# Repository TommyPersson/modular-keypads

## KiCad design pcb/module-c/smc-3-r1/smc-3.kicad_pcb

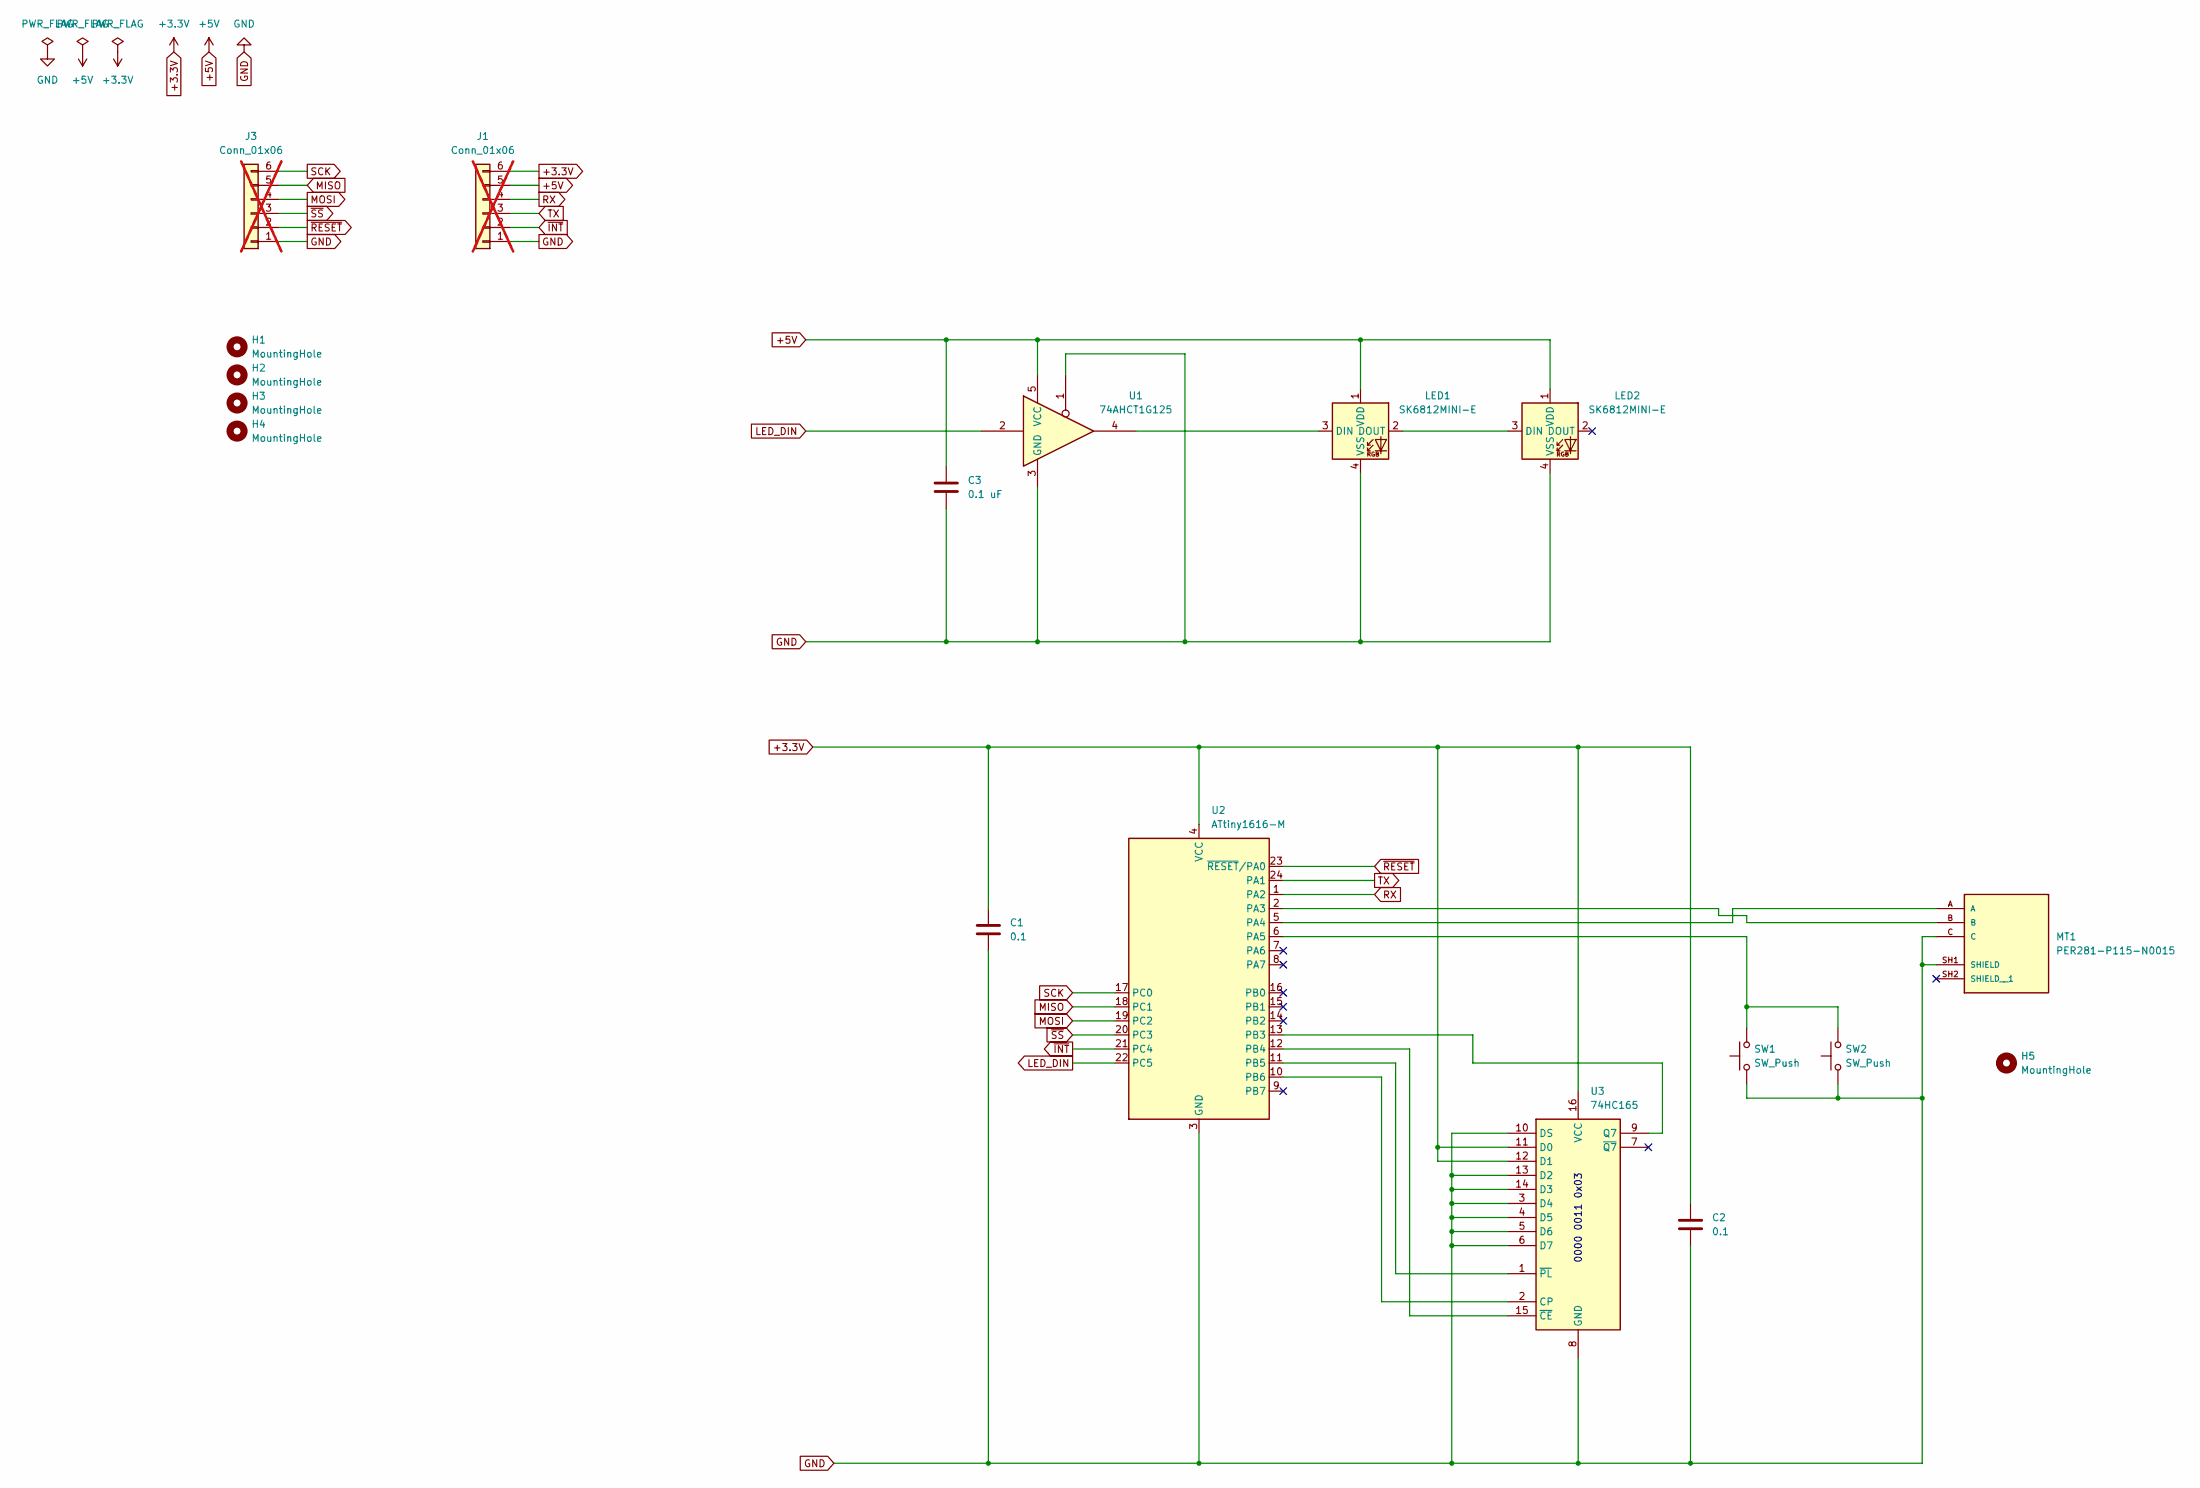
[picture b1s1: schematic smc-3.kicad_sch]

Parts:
C1, C2: 0.1; C_0603_1608Metric
C3: 0.1 uF; C_0603_1608Metric
H1, H2, H3, H4, H5: MountingHole; MountingHole_2.2mm_M2
J1, J3: Conn_01x06; PinHeader_1x06_P2.54mm_Vertical; not fitted
LED1, LED2: SK6812MINI-E; LED_choc_6028R-ROT
MT1: PER281-P115-N0015; XDCR_PER281-P115-N0015; PARTREV 07/21
SW1, SW2: SW_Push; SW_SPST_FSMSM
U1: 74AHCT1G125; SOT-353_SC-70-5
U2: ATtiny1616-M; QFN-24-1EP_4x4mm_P0.5mm_EP2.6x2.6mm
U3: 74HC165; DHVQFN-16-1EP_2.5x3.5mm_P0.5mm_EP1x2mm

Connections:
+3.3V: C1.1, C2.1, J1.6, U2.4 (VCC), U3.11 (D0), U3.12 (D1), U3.16 (VCC)
+5V: C3.1, J1.5, LED1.1 (VDD), LED2.1 (VDD), U1.5 (VCC)
GND: C1.2, C2.2, C3.2, J1.1, J3.1, LED1.4 (VSS), LED2.4 (VSS), MT1.C, MT1.SH1 (SHIELD), SW1.1, SW2.1, U1.1, U1.3 (GND), U2.3 (GND), U2.25 (GND), U3.3 (D4), U3.4 (D5), U3.5 (D6), U3.6 (D7), U3.8 (GND), U3.10 (DS), U3.13 (D2), U3.14 (D3)
LED_DIN: U1.2, U2.22 (PC5)
MISO: J3.5, U2.18 (PC1)
MOSI: J3.4, U2.19 (PC2)
unnamed: LED1.3 (DIN), U1.4
unnamed: LED1.2 (DOUT), LED2.3 (DIN)
unnamed: MT1.B, U2.2 (PA3)
unnamed: MT1.A, U2.5 (PA4)
unnamed: SW1.2, SW2.2, U2.6 (PA5)
unnamed: U2.13 (PB3), U3.9 (Q7)
unnamed: U2.12 (PB4), U3.15 (~CE)
unnamed: U2.11 (PB5), U3.1 (~PL)
unnamed: U2.10 (PB6), U3.2 (CP)
RX: J1.4, U2.1 (PA2)
SCK: J3.6, U2.17 (PC0)
TX: J1.3, U2.24 (PA1)
~INT: J1.2, U2.21 (PC4)
~RESET: J3.2, U2.23 (~RESET/PA0)
~SS: J3.3, U2.20 (PC3)

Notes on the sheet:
0000 0011 0x03

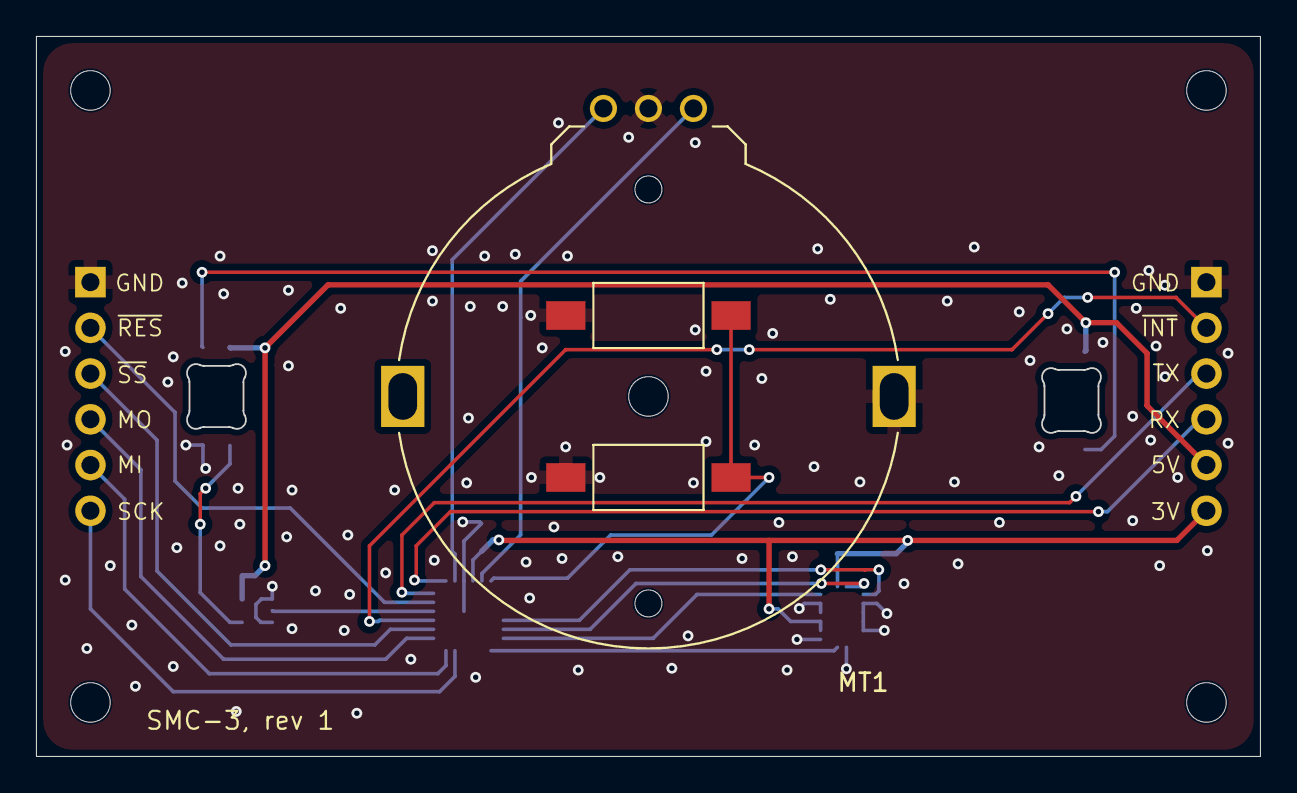
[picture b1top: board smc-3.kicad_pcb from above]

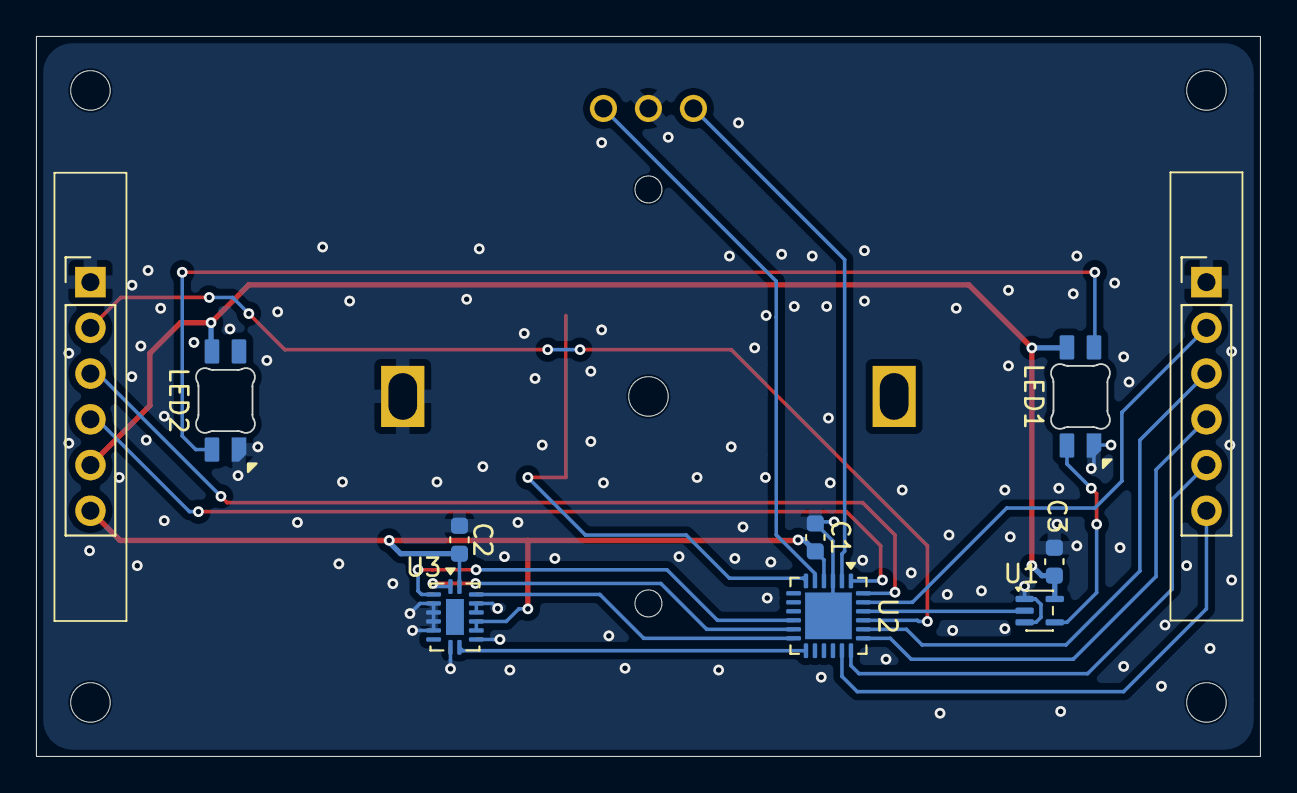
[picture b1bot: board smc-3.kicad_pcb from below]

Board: 4 copper layers, 68.0 x 40.0 mm, 18 parts (10 on the bottom side), 21 nets.

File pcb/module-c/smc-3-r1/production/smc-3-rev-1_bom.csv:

Designator,Footprint,Quantity,Value,LCSC Part #
"C1, C2",0603,2,0.1,
C3,0603,1,0.1 uF,
"J1, J3",PinHeader_1x06_P2.54mm_Vertical,2,Conn_01x06,
"LED1, LED2",LED_choc_6028R-ROT,2,SK6812MINI-E,
MT1,XDCR_PER281-P115-N0015,1,PER281-P115-N0015,
"SW1, SW2",SW_SPST_FSMSM,2,SW_Push,
U1,SOT-353_SC-70-5,1,74AHCT1G125,
U2,QFN-24-1EP_4x4mm_P0.5mm_EP2.6x2.6mm,1,ATtiny1616-M,
U3,DHVQFN-16-1EP_2.5x3.5mm_P0.5mm_EP1x2mm,1,74HC165,
